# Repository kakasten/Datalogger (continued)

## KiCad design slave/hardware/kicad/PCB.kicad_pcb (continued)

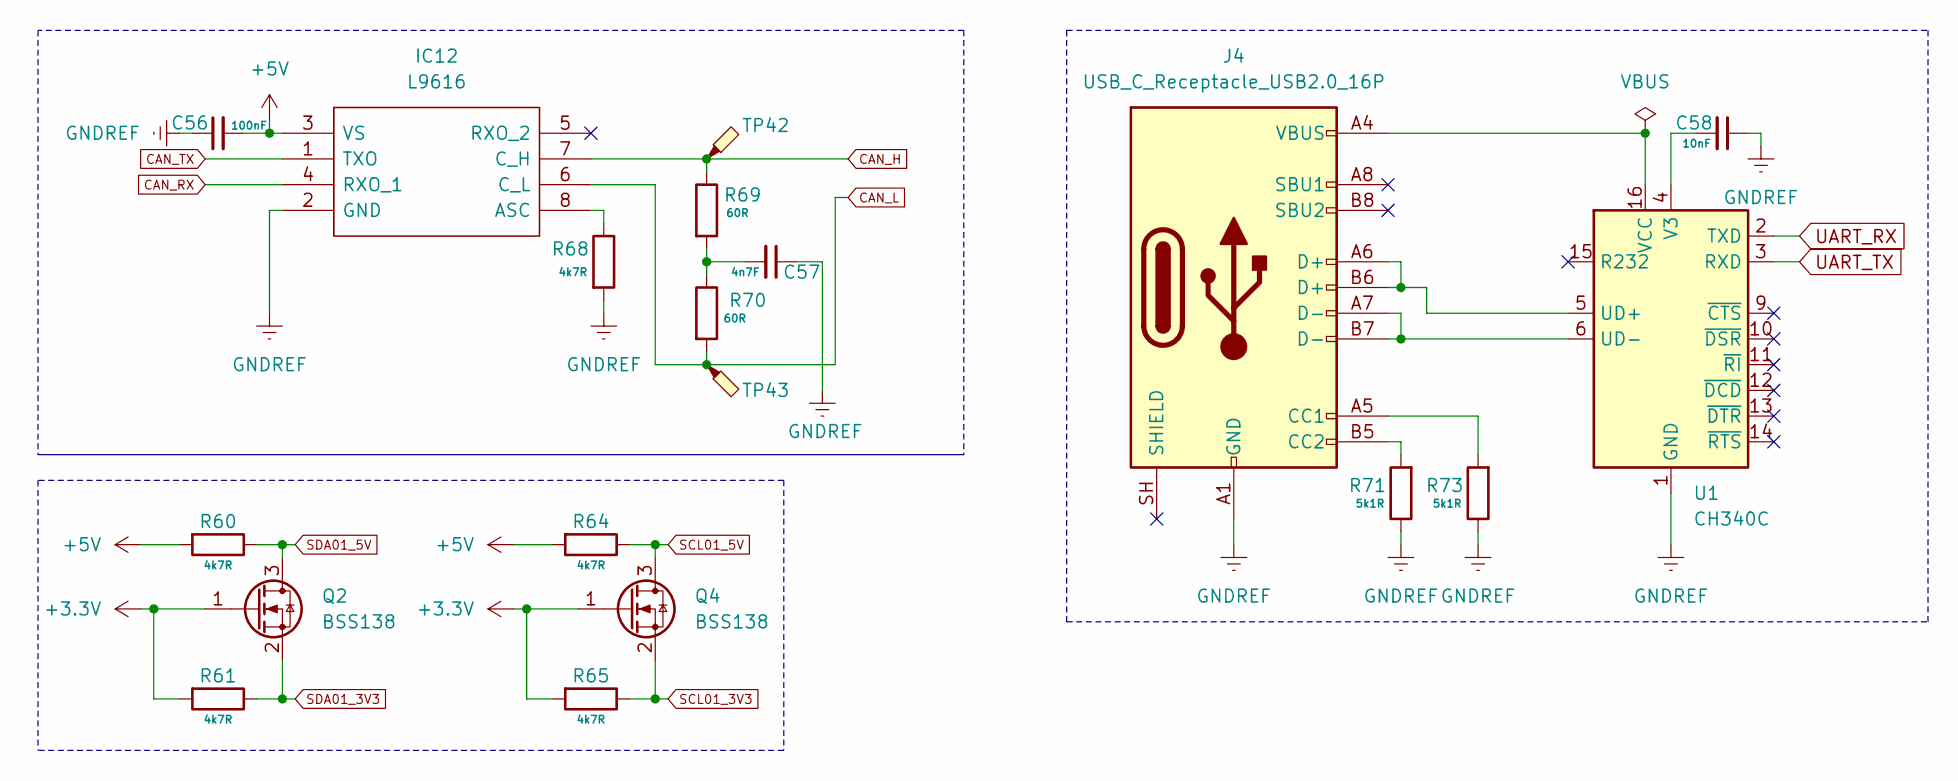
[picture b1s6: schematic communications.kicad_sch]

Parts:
C56: 100nF; C_0603_1608Metric
C57: 4n7F; C_0603_1608Metric
C58: 10nF; C_0603_1608Metric
IC12: L9616; SOIC127P600X175-8N; Mouser Part Number 511-L9616
J4: USB_C_Receptacle_USB2.0_16P; USB_C_Receptacle_HCTL_HC-TYPE-C-16P-01A
Q2, Q4: BSS138; SOT-23
R60, R61, R64, R65, R68: 4k7R; R_0805_2012Metric
R69, R70: 60R; R_0805_2012Metric
R71, R73: 5k1R; R_0603_1608Metric
TP42, TP43: TestPoint_Bridge_Pitch2.0mm_Drill0.7mm
U1: CH340C; SOIC-16_3.9x9.9mm_P1.27mm

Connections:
+3.3V: Q2.1 (G), Q4.1 (G), R61.2, R65.2; also elsewhere on the board
+5V: C56.2, IC12.3 (VS), R60.2, R64.2; also elsewhere on the board
CAN_H: IC12.7 (C_H), R69.1, TP42.1 (1_1); also elsewhere on the board
CAN_L: IC12.6 (C_L), R70.2, TP43.1 (1_1); also elsewhere on the board
CAN_RX: IC12.4 (RXO_1); also elsewhere on the board
CAN_TX: IC12.1 (TXO); also elsewhere on the board
GNDREF: C56.1, C57.1, C58.1, IC12.2 (GND), J4.A1 (GND), J4.A12 (GND), J4.B1 (GND), J4.B12 (GND), R68.2, R71.1, R73.1, U1.1 (GND); also elsewhere on the board
unnamed: C57.2, R69.2, R70.1
unnamed: IC12.8 (ASC), R68.1
unnamed: J4.A5 (CC1), R73.2
unnamed: J4.B5 (CC2), R71.2
unnamed: J4.A6 (D+), J4.B6 (D+), U1.5 (UD+)
unnamed: J4.A7 (D-), J4.B7 (D-), U1.6 (UD-)
unnamed: C58.2, U1.4 (V3)
unnamed: J4.A4 (VBUS), J4.A9 (VBUS), J4.B4 (VBUS), J4.B9 (VBUS), U1.16 (VCC)
SCL01_3V3: Q4.2 (S), R65.1; also elsewhere on the board
SCL01_5V: Q4.3 (D), R64.1; also elsewhere on the board
SDA01_3V3: Q2.2 (S), R61.1; also elsewhere on the board
SDA01_5V: Q2.3 (D), R60.1; also elsewhere on the board
UART_RX: U1.2 (TXD); also elsewhere on the board
UART_TX: U1.3 (RXD); also elsewhere on the board

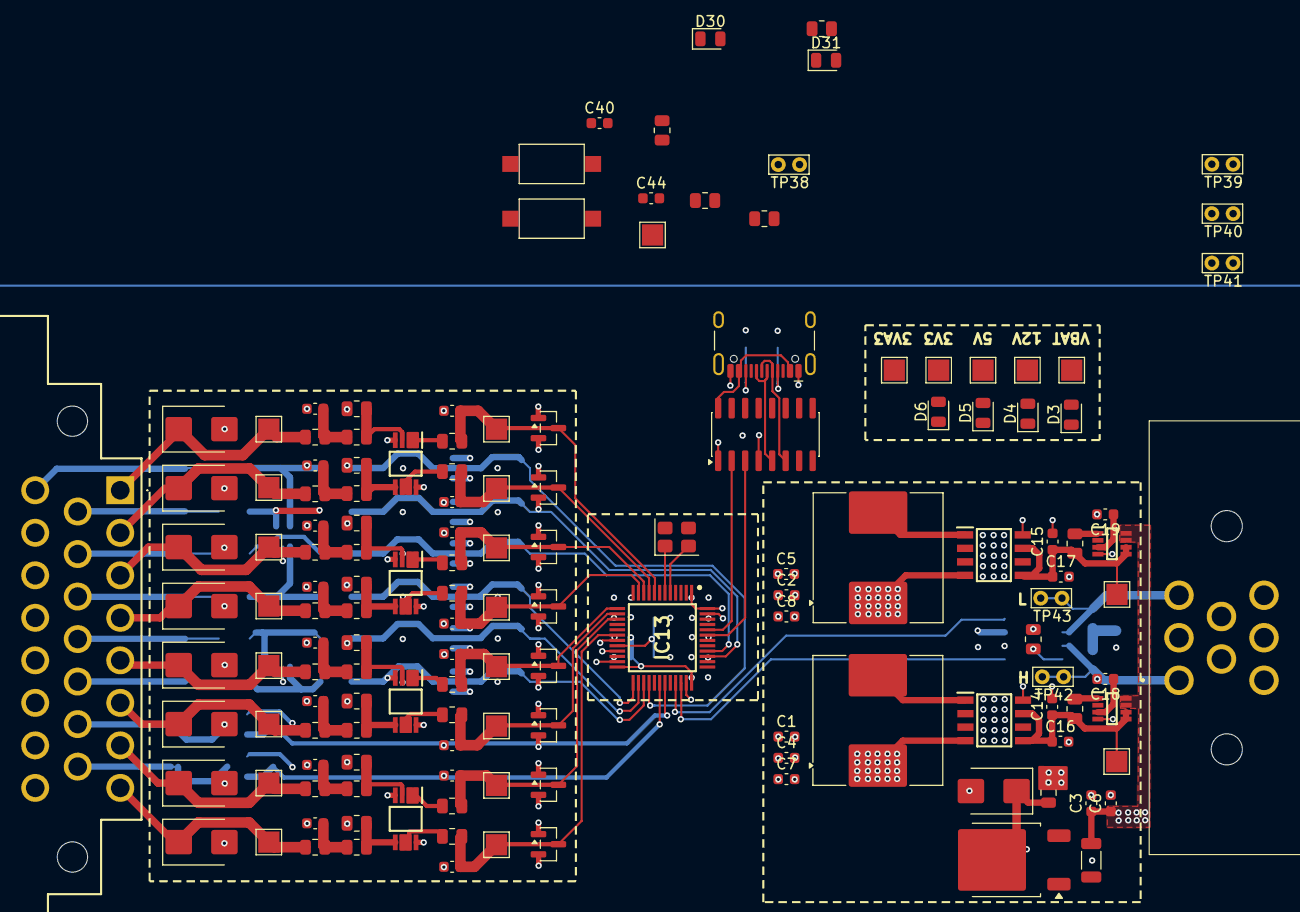
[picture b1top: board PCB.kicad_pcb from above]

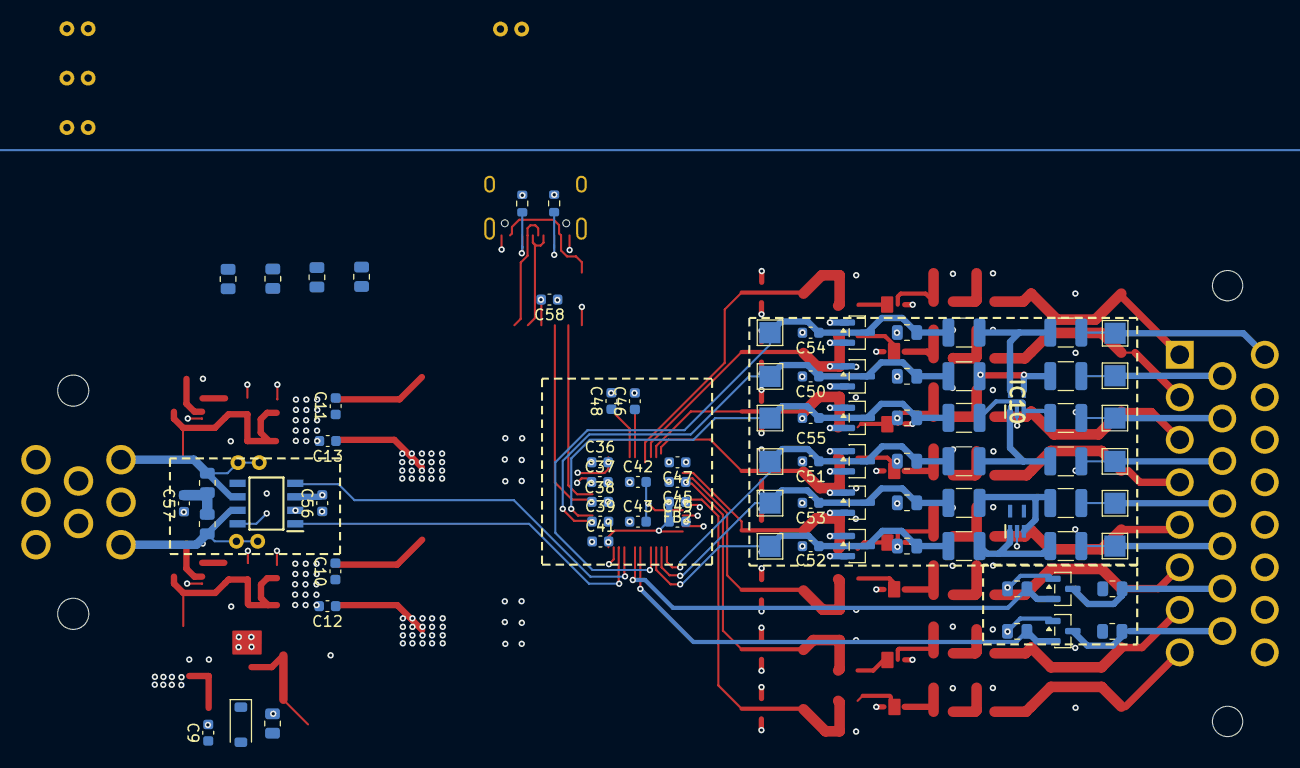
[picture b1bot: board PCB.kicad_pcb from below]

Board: 4 copper layers, 227 parts (82 on the bottom side), 111 nets.

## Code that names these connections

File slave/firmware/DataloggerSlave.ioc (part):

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Mcu.Name=STM32G431C(6-8-B)Tx
Mcu.Package=LQFP48
Mcu.UserName=STM32G431C8Tx
PA0.Mode=IN1-Single-Ended
PA0.Signal=ADC1_IN1
PA1.Mode=IN2-Single-Ended
PA1.Signal=ADC1_IN2
PA11.Mode=FDCAN_Activate
PA11.Signal=FDCAN1_RX
PA12.Mode=FDCAN_Activate
PA12.Signal=FDCAN1_TX
PA13.Mode=Serial_Wire
PA13.Signal=SYS_JTMS-SWDIO
PA14.Mode=Serial_Wire
PA14.Signal=SYS_JTCK-SWCLK
PA15.Signal=S_TIM2_CH1
PA2.Mode=IN3-Single-Ended
PA2.Signal=ADC1_IN3
PA3.Mode=IN4-Single-Ended
PA3.Signal=ADC1_IN4
PA5.Mode=IN13-Single-Ended
PA5.Signal=ADC2_IN13
PA6.Mode=IN3-Single-Ended
PA6.Signal=ADC2_IN3
PA7.Mode=IN4-Single-Ended
PA7.Signal=ADC2_IN4
PA8.Mode=I2C
PA8.Signal=I2C2_SDA
PA9.Mode=I2C
PA9.Signal=I2C2_SCL
PB10.Mode=Asynchronous
PB10.Signal=USART3_TX
PB11.Mode=Asynchronous
PB11.Signal=USART3_RX
PB12.Signal=GPXTI12
PB13.Signal=GPXTI13
PB2.Mode=IN12-Single-Ended
PB2.Signal=ADC2_IN12
PB3.Signal=S_TIM2_CH2
PB7.Mode=I2C
PB7.Signal=I2C1_SDA
PB8-BOOT0.Mode=I2C
PB8-BOOT0.Signal=I2C1_SCL
PC13.Signal=GPIO_Output
PC14-OSC32_IN.Signal=GPIO_Output
PC15-OSC32_OUT.Signal=GPIO_Output
PF0-OSC_IN.Signal=GPXTI0
PF1-OSC_OUT.Signal=GPXTI1
RCC.HSE_VALUE=8000000
RCC.SYSCLKFreq_VALUE=16000000
board=custom
